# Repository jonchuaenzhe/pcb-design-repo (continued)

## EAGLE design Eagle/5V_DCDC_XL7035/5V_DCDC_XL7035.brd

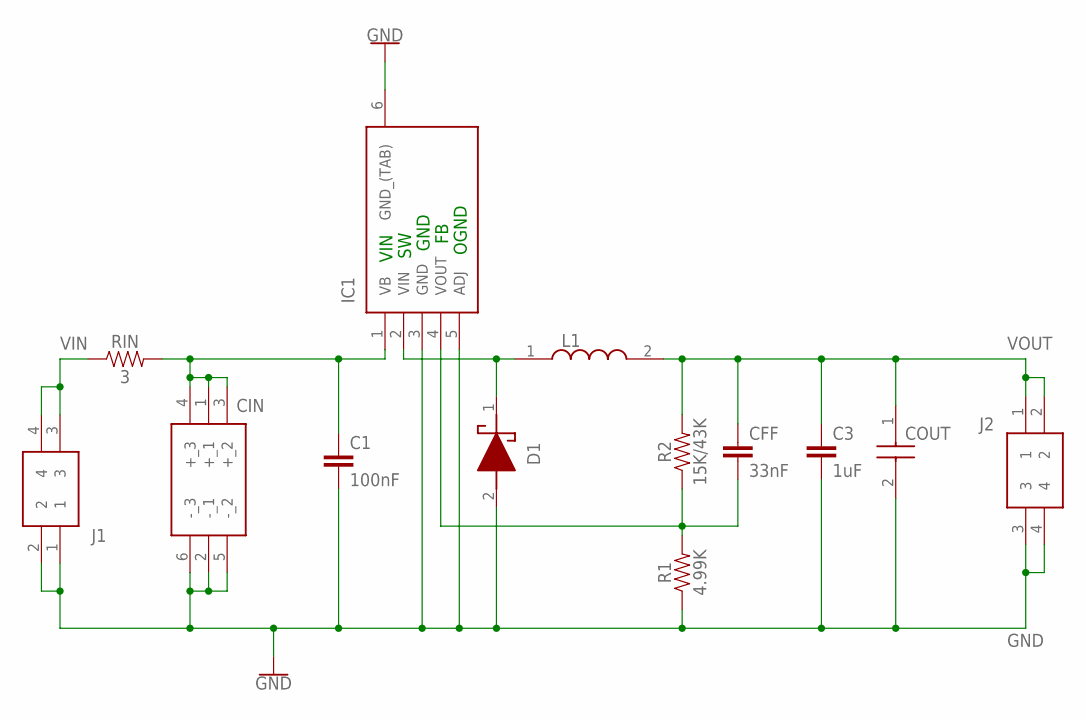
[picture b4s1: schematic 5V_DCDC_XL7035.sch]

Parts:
C1: 100nF; 0603
C3: 1uF; 0603
CFF: 33nF; 0603
CIN: EEE-FK1K101AV; EEEFK0J332AV
COUT: EMK325ABJ107MM-T; CAPC3225X270N
D1: S310; DIONM8059X265N
IC1: UC285TDKTTT-ADJ; TO170P1524X483-6N
J1, J2: 691411510002
L1: SRR1280-101M; INDPM125125X800N
R1: 4.99K; 0603
R2: 15K/43K; 0603
RIN: 3; 1206

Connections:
GND: C1.2, C3.2, CIN.2 (-_1), CIN.5 (-_2), CIN.6 (-_3), COUT.2, D1.2 (A), IC1.3 (GND), IC1.5 (ADJ), IC1.6 (GND_(TAB)), J1.1, J1.2, J2.3, J2.4, R1.1
unnamed: C1.1, CIN.1 (+_1), CIN.3 (+_2), CIN.4 (+_3), IC1.1 (VB), RIN.2
unnamed: D1.1 (K), IC1.2 (VIN), L1.1
unnamed: CFF.2, IC1.4 (VOUT), R1.2, R2.1
VIN: J1.3, J1.4, RIN.1
VOUT: C3.1, CFF.1, COUT.1, J2.1, J2.2, L1.2, R2.2

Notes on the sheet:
VIN
GND
OGND

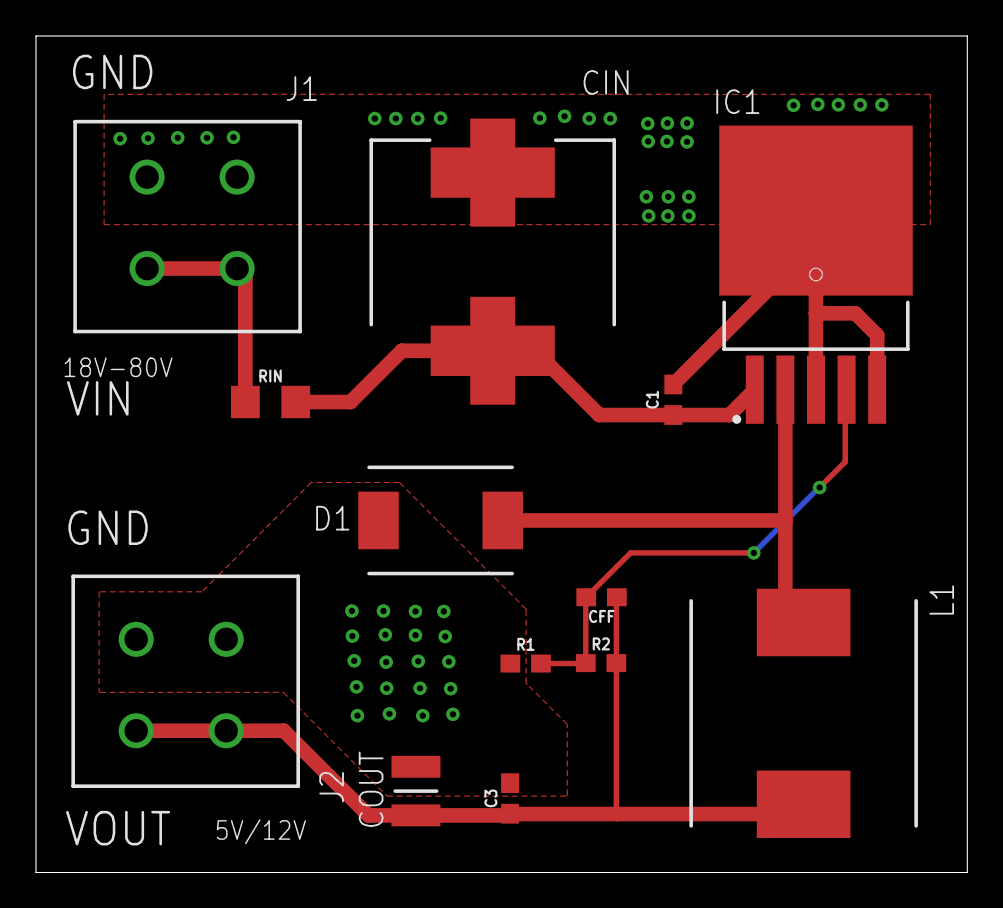
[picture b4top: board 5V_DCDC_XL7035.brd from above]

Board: 2 copper layers, 51.7 x 46.5 mm, 13 parts (0 on the bottom side), 6 nets.

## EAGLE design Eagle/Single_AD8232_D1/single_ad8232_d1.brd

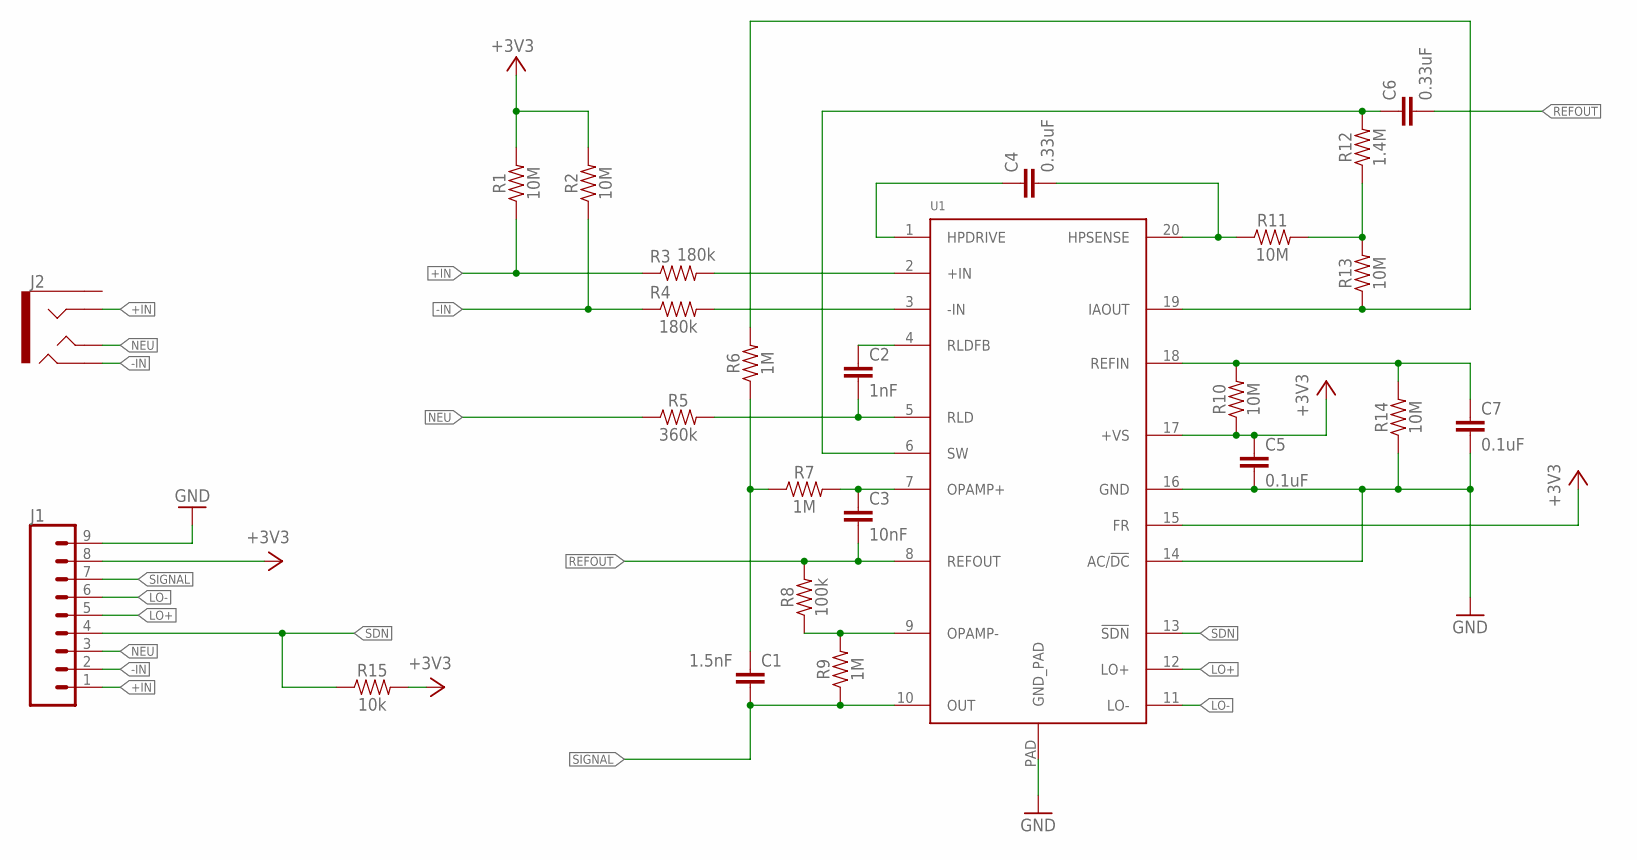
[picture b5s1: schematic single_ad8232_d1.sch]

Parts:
C1: 1.5nF; 0603-CAP
C2: 1nF; 0603-CAP
C3: 10nF; 0603-CAP
C4, C6: 0.33uF; 0805
C5, C7: 0.1uF; 0603-CAP
J1: CONN_09; 1X09
J2: AUDIO_JACK_TRRSSMD_RA; AUDIO_JACK_3.5MM_TRRS_SMD_RA
R1, R2, R10, R11, R13, R14: 10M; 0603
R3, R4: 180k; 0603
R5: 360k; 0603
R6, R7, R9: 1M; 0603
R8: 100k; 0603
R12: 1.4M; 0603
R15: 10k; 0603
U1: AD8232ACPZ-R7; LFCSP_20

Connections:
+3V3: C5.1, J1.8, R1.2, R2.2, R10.1, R15.2, U1.15 (FR), U1.17 (+VS)
+IN: J1.1, J2.RING1, R1.1, R3.1
-IN: J1.2, J2.RING2, R2.1, R4.1
GND: C5.2, C7.2, J1.9, R14.1, U1.14 (AC/!DC), U1.16 (GND), U1.PAD (GND_PAD)
LO+: J1.5, U1.12 (LO+)
LO-: J1.6, U1.11 (LO-)
unnamed: R8.1, R9.2, U1.9 (OPAMP-)
unnamed: R3.2, U1.2 (+IN)
unnamed: R4.2, U1.3 (-IN)
unnamed: C1.1, R6.1, R7.1
unnamed: C3.1, R7.2, U1.7 (OPAMP+)
unnamed: C2.1, U1.4 (RLDFB)
unnamed: C2.2, R5.2, U1.5 (RLD)
unnamed: R6.2, R13.1, U1.19 (IAOUT)
unnamed: C6.1, R12.2, U1.6 (SW)
unnamed: C7.1, R10.2, R14.2, U1.18 (REFIN)
unnamed: R11.2, R12.1, R13.2
unnamed: C4.2, R11.1, U1.20 (HPSENSE)
unnamed: C4.1, U1.1 (HPDRIVE)
NEU: J1.3, J2.TIP, R5.1
REFOUT: C3.2, C6.2, R8.2, U1.8 (REFOUT)
SDN: J1.4, R15.1, U1.13 (!SDN)
SIGNAL: C1.2, J1.7, R9.1, U1.10 (OUT)

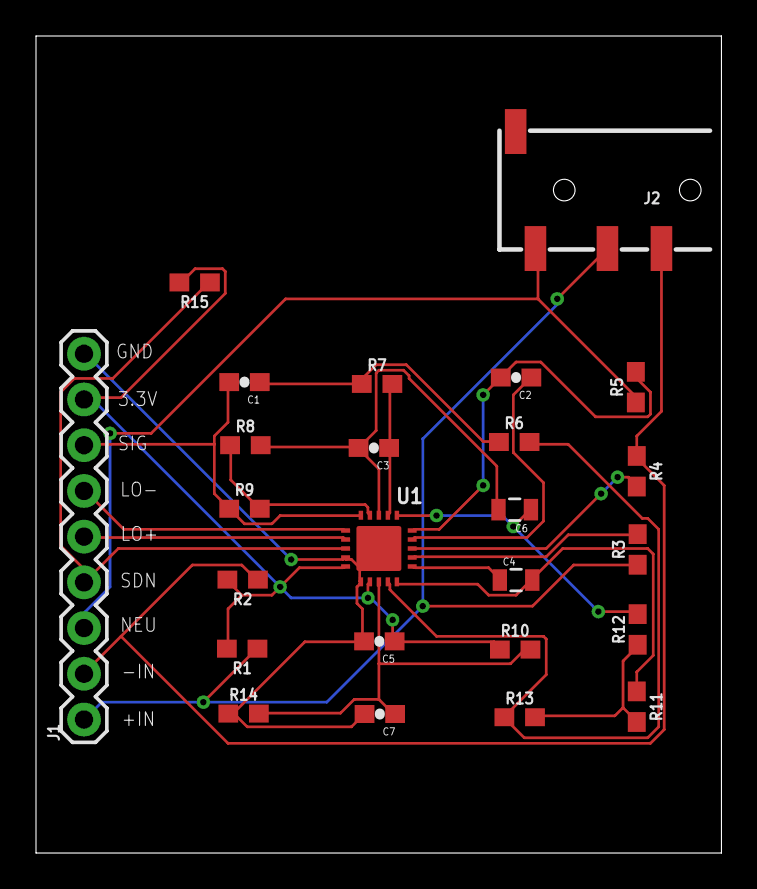
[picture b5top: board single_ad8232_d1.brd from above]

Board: 2 copper layers, 38.1 x 45.4 mm, 25 parts (0 on the bottom side), 23 nets.

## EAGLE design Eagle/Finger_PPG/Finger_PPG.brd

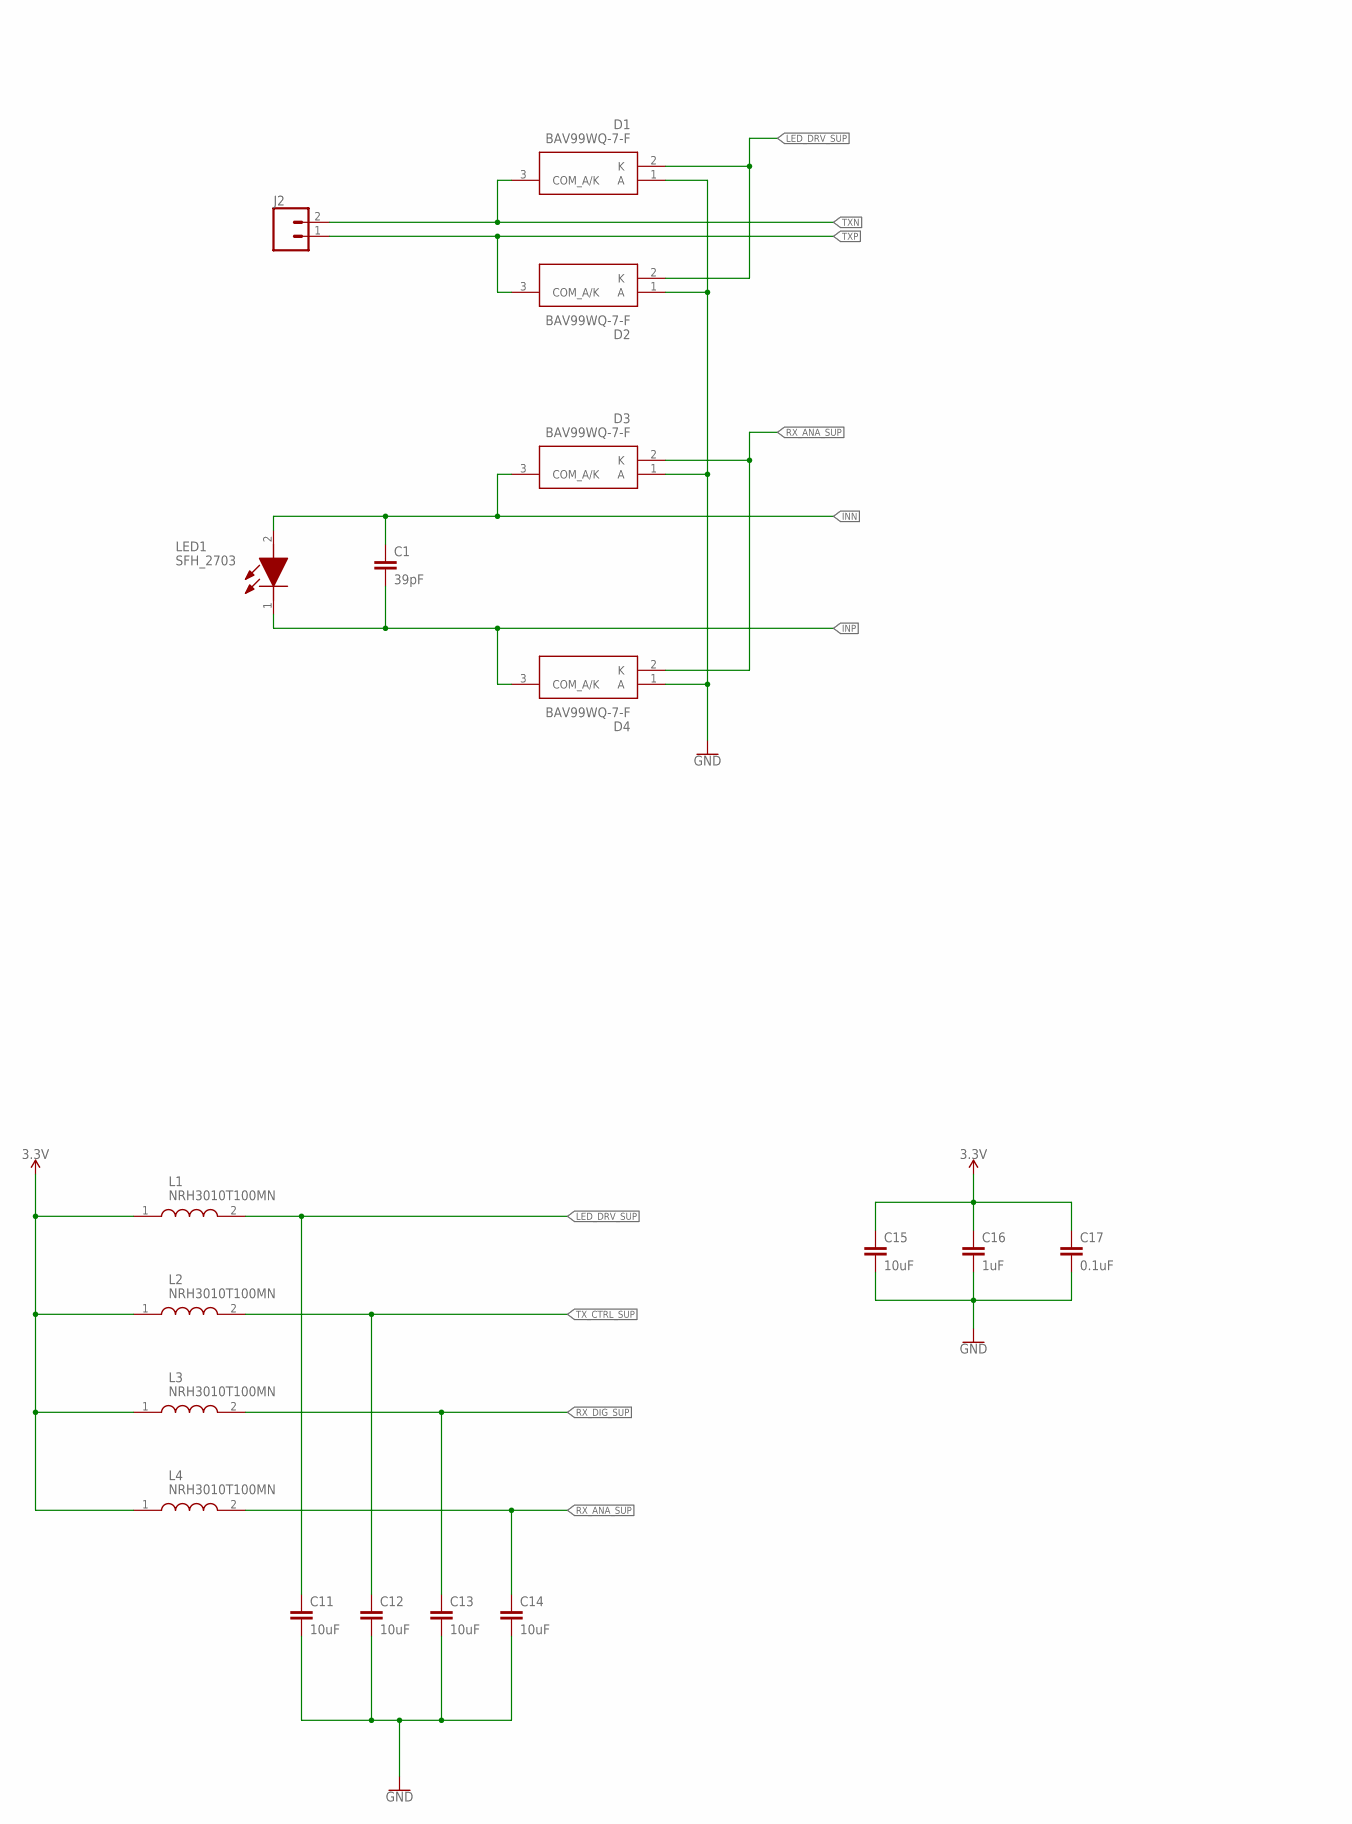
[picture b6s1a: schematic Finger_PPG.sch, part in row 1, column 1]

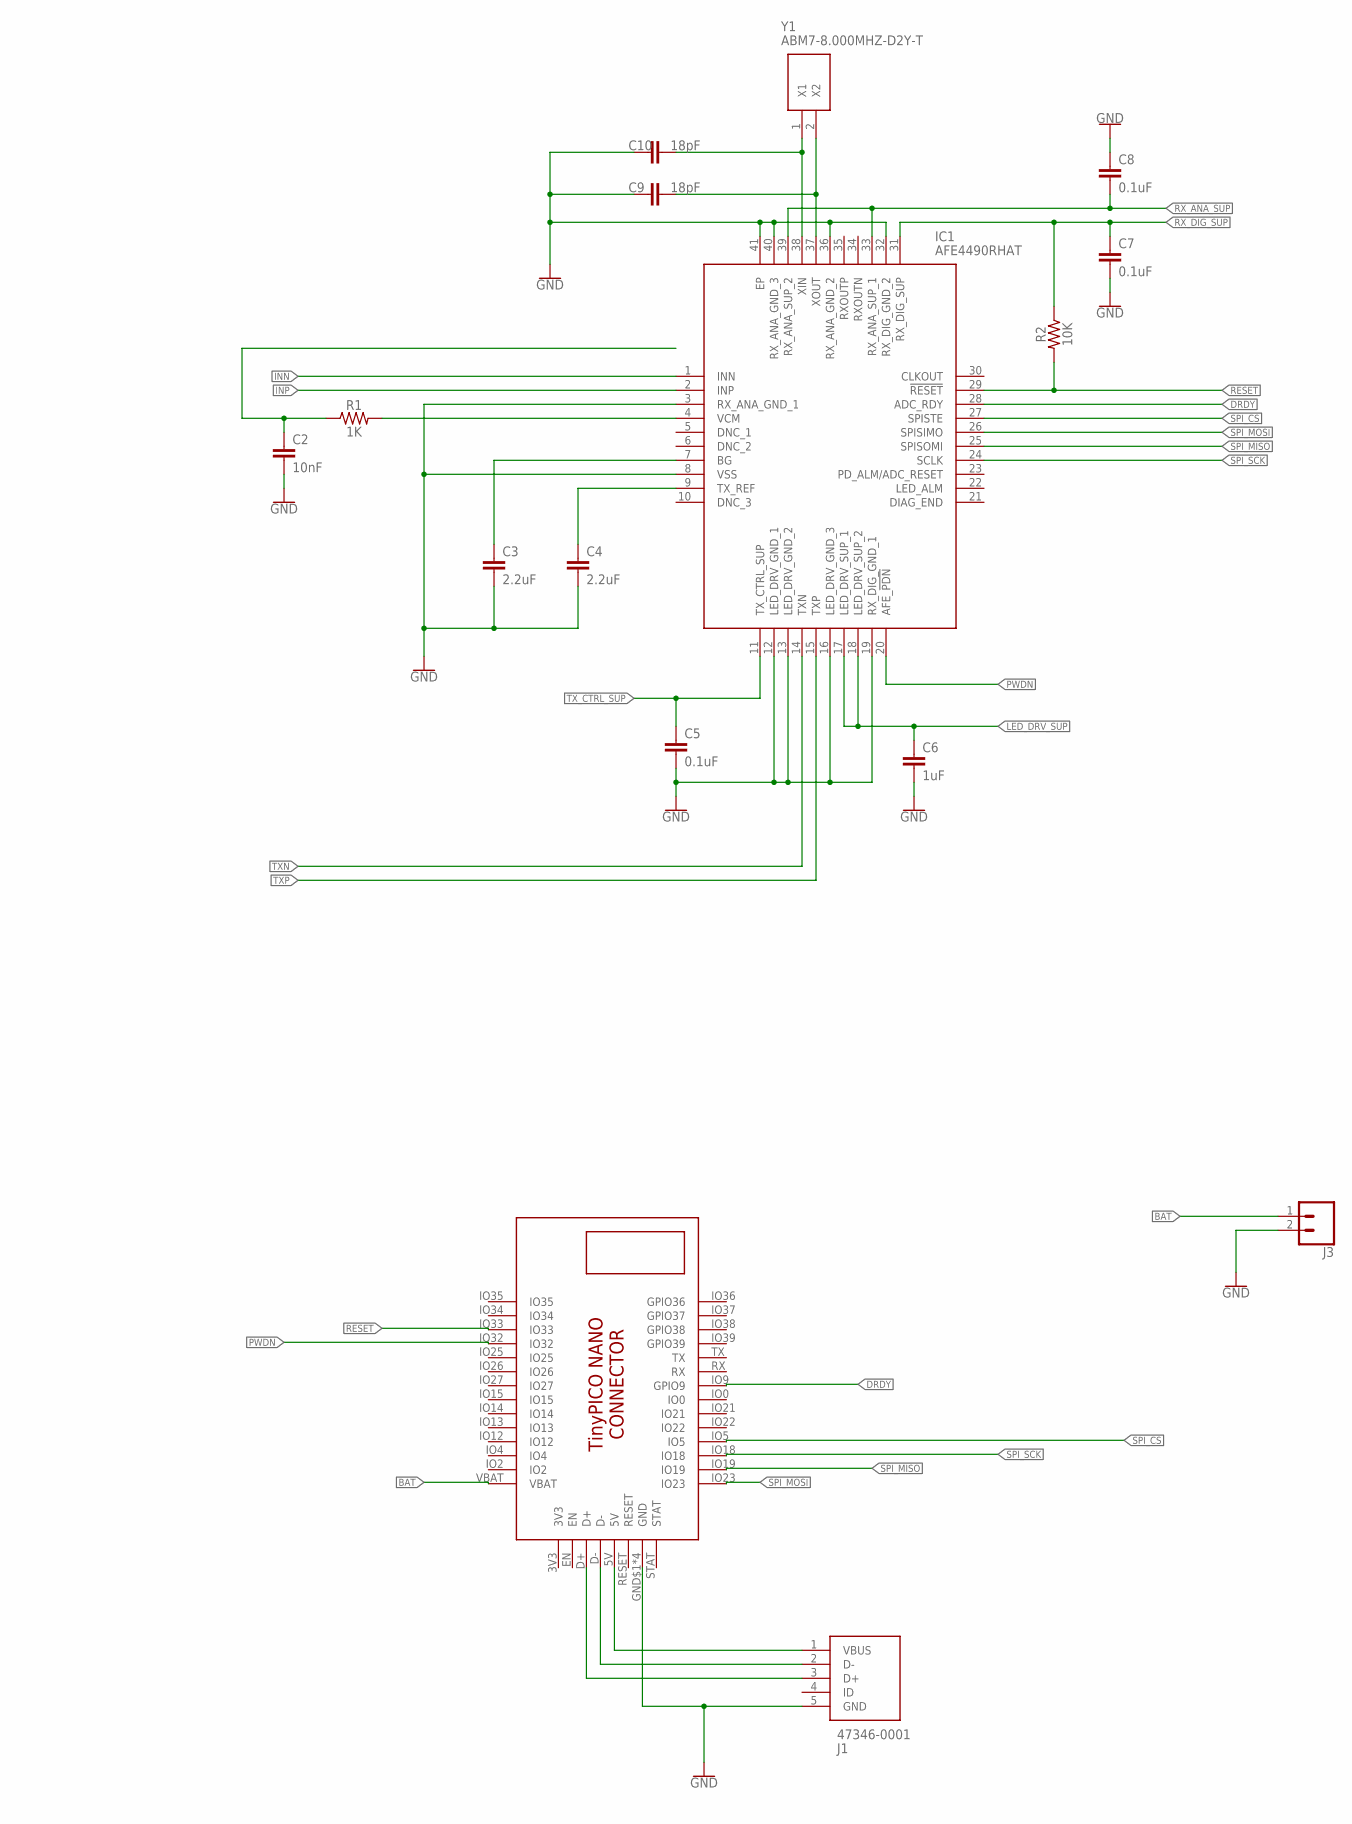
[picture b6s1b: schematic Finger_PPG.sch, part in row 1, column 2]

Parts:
C1: 39pF; 0402
C2: 10nF; 0402
C3, C4: 2.2uF; 0603
C5, C7, C8, C17: 0.1uF; 0402
C6, C16: 1uF; 0402
C9, C10: 18pF; 0402
C11, C12, C13, C14, C15: 10uF; 0805
D1, D2, D3, D4: BAV99WQ-7-F; SOT65P210X110-3N
IC1: AFE4490RHAT; QFN50P600X600X100-41N
J1: 47346-0001
J2, J3: CONN_02; 1X02
L1, L2, L3, L4: NRH3010T100MN
LED1: SFH_2703; SFH2703
R1: 1K; 0402
R2: 10K; 0402
U$1: TINYPICO-NANO-CONNECTOR
Y1: ABM7-8.000MHZ-D2Y-T; ABM78000MHZD2YT

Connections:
3.3V: C15.1, C16.1, C17.1, L1.1, L2.1, L3.1, L4.1
3V3: U$1.3V3
BAT: J3.1, U$1.VBAT
DRDY: IC1.28 (ADC_RDY), U$1.IO9 (GPIO9)
GND: C2.2, C3.2, C4.2, C5.2, C6.2, C7.2, C8.1, C9.1, C10.1, C11.2, C12.2, C13.2, C14.2, C15.2, C16.2, C17.2, D1.1 (A), D2.1 (A), D3.1 (A), D4.1 (A), IC1.3 (RX_ANA_GND_1), IC1.8 (VSS), IC1.12 (LED_DRV_GND_1), IC1.13 (LED_DRV_GND_2), IC1.16 (LED_DRV_GND_3), IC1.19 (RX_DIG_GND_1), IC1.32 (RX_DIG_GND_2), IC1.36 (RX_ANA_GND_2), IC1.40 (RX_ANA_GND_3), IC1.41 (EP), J1.5 (GND), J3.2, U$1.GND$1 (GND), U$1.GND$2 (GND), U$1.GND$3 (GND), U$1.GND$4 (GND)
INN: C1.1, D3.3 (COM_A/K), IC1.1 (INN), LED1.2 (A)
INP: C1.2, D4.3 (COM_A/K), IC1.2 (INP), LED1.1 (K)
LED_DRV_SUP: C6.1, C11.1, D1.2 (K), D2.2 (K), IC1.17 (LED_DRV_SUP_1), IC1.18 (LED_DRV_SUP_2), L1.2
unnamed: IC1.4 (VCM), R1.2
unnamed: C2.1, R1.1
unnamed: C3.1, IC1.7 (BG)
unnamed: C4.1, IC1.9 (TX_REF)
unnamed: C10.2, IC1.38 (XIN), Y1.1 (X1)
unnamed: C9.2, IC1.37 (XOUT), Y1.2 (X2)
unnamed: J1.1 (VBUS), U$1.5V
unnamed: J1.2 (D-), U$1.D-
unnamed: J1.3 (D+), U$1.D+
PWDN: IC1.20 (AFE_!PDN), U$1.IO32
RESET: IC1.29 (!RESET), R2.2, U$1.IO33
RX_ANA_SUP: C8.2, C14.1, D3.2 (K), D4.2 (K), IC1.33 (RX_ANA_SUP_1), IC1.39 (RX_ANA_SUP_2), L4.2
RX_DIG_SUP: C7.1, C13.1, IC1.31 (RX_DIG_SUP), L3.2, R2.1
SPI_CS: IC1.27 (SPISTE), U$1.IO5
SPI_MISO: IC1.25 (SPISOMI), U$1.IO19
SPI_MOSI: IC1.26 (SPISIMO), U$1.IO23
SPI_SCK: IC1.24 (SCLK), U$1.IO18
TXN: D1.3 (COM_A/K), IC1.14 (TXN), J2.2
TXP: D2.3 (COM_A/K), IC1.15 (TXP), J2.1
TX_CTRL_SUP: C5.1, C12.1, IC1.11 (TX_CTRL_SUP), L2.2

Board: 2 copper layers, 34 parts (0 on the bottom side), 27 nets, no tracks yet.

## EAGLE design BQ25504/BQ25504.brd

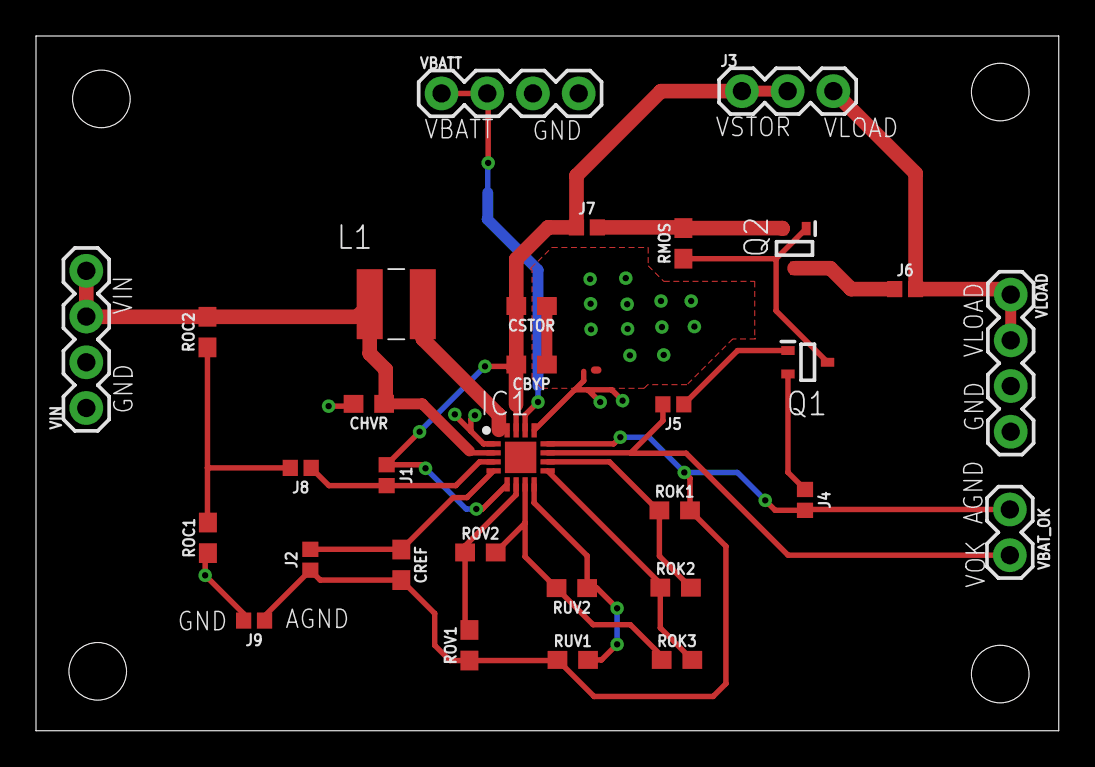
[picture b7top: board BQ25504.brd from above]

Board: 2 copper layers, 56.8 x 38.6 mm, 31 parts (0 on the bottom side), 21 nets.

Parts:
CBYP: 0.01uF; 0603
CHVR: 4.7uF; 0603
CREF: 0.01uF; 0603
CSTOR: 4.7uF; 0603
IC1: BQ25504RGTR; QFN50P300X300X100-17N
J1, J2, J4, J5, J6, J7, J8, J9: 0; 0402
J3: 1X03
L1: LPS4018-223MRC; LPS4018223MRC
Q1: BSS138WH6433XTMA1; SOT65P210X100-3N
Q2: BSS223PWH6327XTSA1; SOT65P210X100-3N
RMOS: 1M; 0603
ROC1, ROC2: 10M; 0603
ROK1: 2.67M; 0603
ROK2: 2.32M; 0603
ROK3: 5.1M; 0603
ROV1: 3.6M; 0603
ROV2: 6.2M; 0603
RUV1: 5.6M; 0603
RUV2: 4.32M; 0603
VBATT: 1X04
VBAT_OK: 1X02
VIN: 1X04
VLOAD: 1X04

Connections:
AGND: CREF.2, IC1.12, J2.1, J4.2, J9.1, ROK1.2, ROV1.1, RUV1.1, VBAT_OK.2
GND: CBYP.1, CHVR.2, CSTOR.1, IC1.1, IC1.13, J9.2, ROC1.1, VBATT.3, VBATT.4, VIN.1, VIN.2, VLOAD.3, VLOAD.4
unnamed: CREF.1, IC1.4, J2.2
unnamed: CHVR.1, IC1.2, L1.1, ROC2.2, VIN.3, VIN.4
unnamed: J8.2, ROC1.2, ROC2.1
unnamed: IC1.7, ROK3.1, ROV2.2, RUV2.2
unnamed: IC1.6, ROV1.2, ROV2.1
unnamed: IC1.8, RUV1.2, RUV2.1
unnamed: J4.1, Q1.2
unnamed: IC1.11, J5.2, VBAT_OK.1
unnamed: IC1.9, ROK2.1, ROK3.2
unnamed: IC1.10, ROK1.1, ROK2.2
unnamed: IC1.16, L1.2
unnamed: J3.3, J6.2, VLOAD.1, VLOAD.2
unnamed: Q1.3, Q2.1, RMOS.1
unnamed: J5.1, Q1.1
unnamed: IC1.14, VBATT.1, VBATT.2
unnamed: J7.2, Q2.2, RMOS.2
unnamed: J6.1, Q2.3
unnamed: IC1.3, J1.2, J8.1
VSTOR: CBYP.2, CSTOR.2, IC1.5, IC1.15, J1.1, J3.1, J3.2, J7.1

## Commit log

2022-07-15 added BQ25504
2022-07-15 added all files
2022-07-26 modified readme
